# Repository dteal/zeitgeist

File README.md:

# zeitgeist

We're building a robotic grocery cart.

## audio

The materials for experimentation in tracking a ultrasonic sound source (phone) from a microphone array. Tracking works up to at most a couple feet with ~30 degree resolution (not near good enough for a robot cart inside a grocery store).

## control

Programs to control a new, monolithic hoverboard control board from a Raspberry Pi.

## cv

Scripts related to Kinect-based computer vision for tracking a customer and detecting obstacles.

## serial

Files (scripts and PCB sources) used for decoding serial communication in between the two boards that controlled the original hoverboard. This communication bus could be read to determine the state of each hoverboard side (angle, wheel speed, etc), but could not be written to, making it unusable for hoverboard control from an external computer.

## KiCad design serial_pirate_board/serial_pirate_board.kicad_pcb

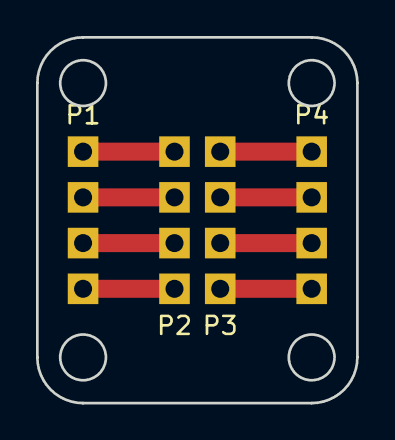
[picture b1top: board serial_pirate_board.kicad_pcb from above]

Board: 2 copper layers, 17.8 x 20.3 mm, 4 parts (0 on the bottom side), 8 nets.

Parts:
P1, P2, P3, P4: CONN_01X04; channel

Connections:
unnamed: P1.1, P2.4
unnamed: P1.2, P2.3
unnamed: P1.3, P2.2
unnamed: P1.4, P2.1
unnamed: P3.1, P4.4
unnamed: P3.2, P4.3
unnamed: P3.3, P4.2
unnamed: P3.4, P4.1

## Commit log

2018-10-24 Added license.
2018-10-24 Added readme.
2018-10-24 Added initial audio code.
2018-10-24 Basic audio input working.
2018-10-29 Switching to non-Kinect audio.
2018-10-29 Removed Kinect audio files for non-Kinect audio switch.
2018-10-29 Finished proof-of-concept DSP algorithm.
2018-10-29 Sample sound generator.
2018-10-30 Finished simulation, tramistted sound generator.
2018-10-30 Fixed WAV file format.
2018-10-31 Finished Python and GRC audio testing.
2018-10-31 Basic object tracking is working.
2018-10-31 Proof-of-concent Kinect obstacle and tracking done.
2018-11-05 Added hoverboard pirate board, debugging code.
2018-11-05 Added some of reverse-engineered protocol.
2018-11-11 Finished serial testing, organized directories.
2018-11-13 Added basic wheel control program.
2018-11-14 Added robot program.
2018-11-14 Fixed robot code typo.
2018-11-14 Starting to add multiprocessing.
2018-11-14 Robot control prototype done.
2018-11-14 Added basic host file.
2018-11-14 Robot progress.
2018-11-29 Updated control scheme with realtime arcade.
2018-11-29 Updated robot control scheme.
2018-11-29 Updated CV code.
2018-11-30 Better computer vision!
2018-12-01 Basic CV and tracking working on Pi.
2018-12-01 Updated CV routines.
2018-12-01 Added joystick control.
2018-12-01 Working status!
2018-12-01 It works!
2018-12-01 More accurate follow estimation.
